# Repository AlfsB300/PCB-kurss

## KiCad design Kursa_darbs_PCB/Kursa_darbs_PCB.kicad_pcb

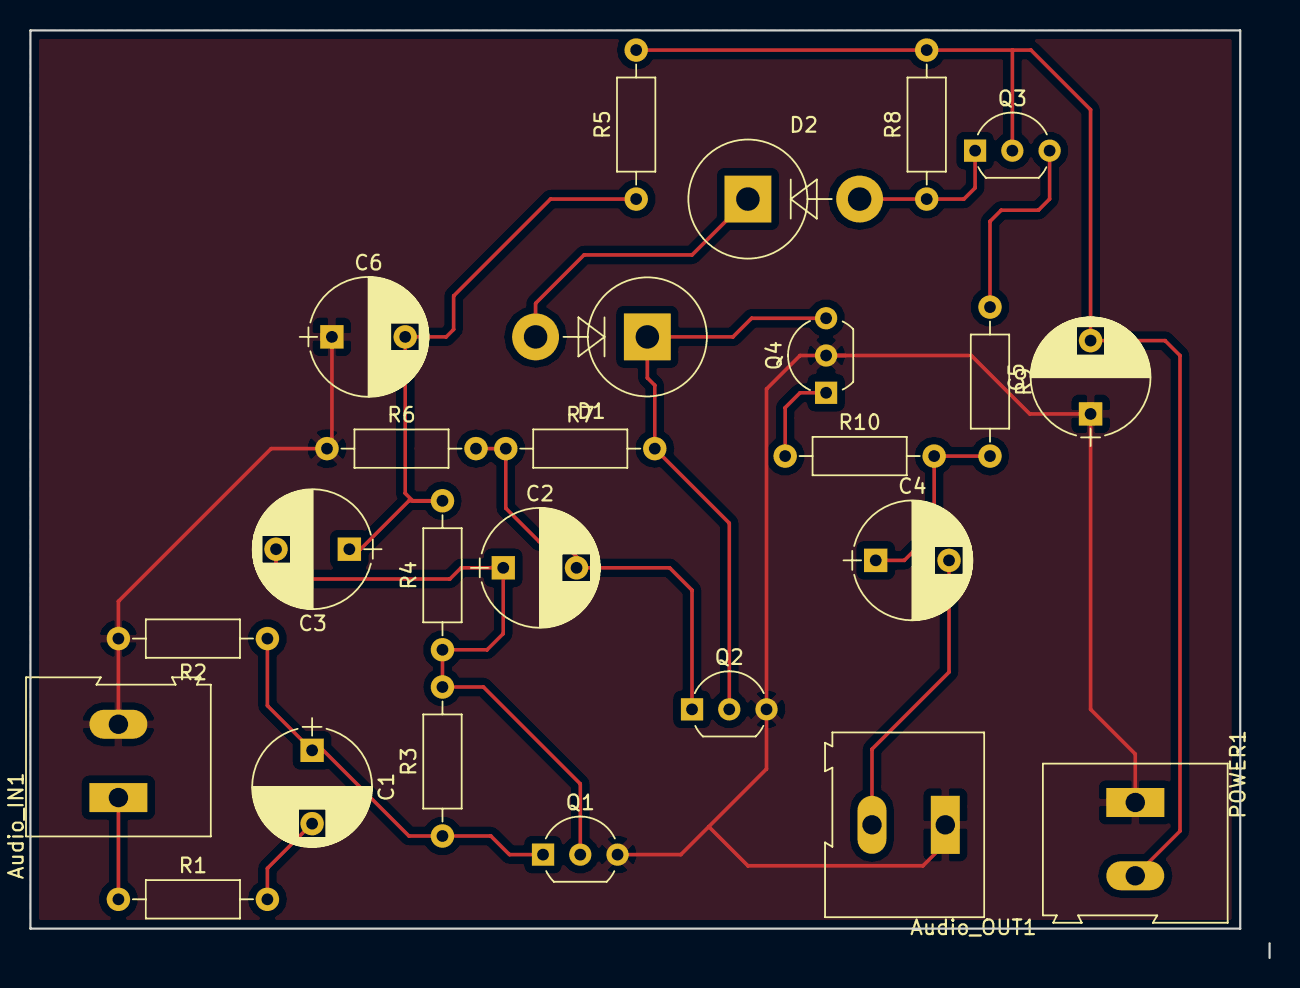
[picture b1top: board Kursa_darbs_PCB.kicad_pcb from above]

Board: 2 copper layers, 84.5 x 63.2 mm, 25 parts (0 on the bottom side), 15 nets.

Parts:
Audio_IN1: Screw_Terminal_1x02; AK300-2
Audio_OUT1: Screw_Terminal_1x02; AK300-2
C1, C6: 10uF; CP_Radial_D8.0mm_P5.00mm
C2: 15uF; CP_Radial_D8.0mm_P5.00mm
C3: 33nF; CP_Radial_D8.0mm_P5.00mm
C4: 220uF; CP_Radial_D8.0mm_P5.00mm
C5: 100uF; CP_Radial_D8.0mm_P5.00mm
D1, D2: 1N4148; D_5KPW_P7.62mm_Vertical_AnodeUp
POWER1: Screw_Terminal_1x02; AK300-2
Q1, Q2, Q3: 2N2222; TO-92_Inline_Wide
Q4: 2N2907; TO-92_Inline_Wide
R1, R4, R8: 1K; R_Axial_DIN0207_L6.3mm_D2.5mm_P10.16mm_Horizontal
R2: 47K; R_Axial_DIN0207_L6.3mm_D2.5mm_P10.16mm_Horizontal
R3: 150K; R_Axial_DIN0207_L6.3mm_D2.5mm_P10.16mm_Horizontal
R5: 470; R_Axial_DIN0207_L6.3mm_D2.5mm_P10.16mm_Horizontal
R6, R7: 33K; R_Axial_DIN0207_L6.3mm_D2.5mm_P10.16mm_Horizontal
R9, R10: 4.7 ohm; R_Axial_DIN0207_L6.3mm_D2.5mm_P10.16mm_Horizontal

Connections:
+5V: C5.2, POWER1.2, Q3.2, R5.2, R8.2
Earth: Audio_IN1.2, Audio_OUT1.1, C5.1, C6.1, POWER1.1, Q1.3, Q2.3, Q4.2, R2.2, R6.1
unnamed: Audio_IN1.1, R1.1
unnamed: Audio_OUT1.2, C4.2
unnamed: C1.1, Q1.1, R2.1, R3.1
unnamed: C1.2, R1.2
unnamed: C2.1, C3.2, Q1.2, R3.2, R4.1
unnamed: C2.2, Q2.1, R6.2, R7.1
unnamed: C3.1, C6.2, R4.2, R5.1
unnamed: C4.1, R9.2, R10.2
unnamed: D1.1, Q2.2, Q4.3, R7.2
unnamed: D1.2, D2.1
unnamed: D2.2, Q3.1, R8.1
unnamed: Q3.3, R9.1
unnamed: Q4.1, R10.1

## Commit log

2017-03-16 pievieno github
2017-03-22 PWR_SUPPLY
2017-03-23 rule_chek
2017-03-30 single_amp
2017-06-16 Kursa_darbs_PCB
